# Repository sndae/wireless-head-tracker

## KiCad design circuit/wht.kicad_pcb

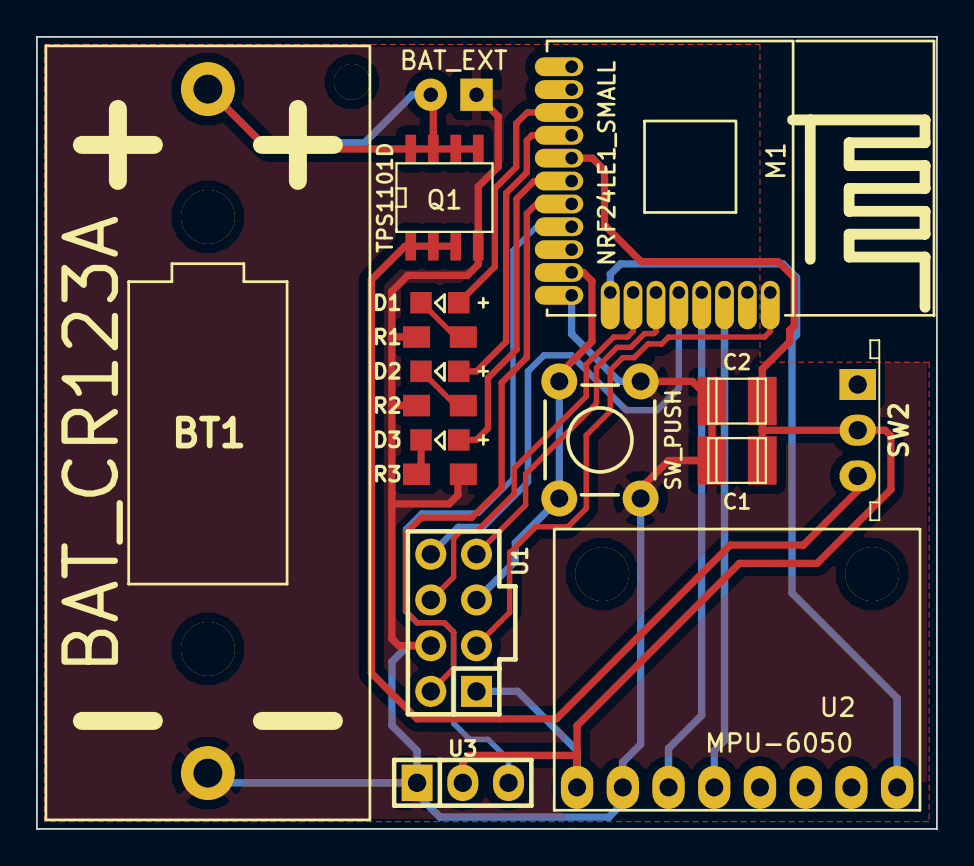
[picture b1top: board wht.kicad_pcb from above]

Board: 2 copper layers, 50.0 x 44.0 mm, 17 parts (0 on the bottom side), 20 nets.

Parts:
BT1: BAT_CR123A; CR123
BT2: BAT_EXT; BATTERY_EXT
C1: C; c_1210
C2: CP1; c_1210
D1, D2, D3: LED; LED-0805
M1: NRF24LE1_SMALL
Q1: TPS1101D; SOIC-8_N
R1, R2, R3: R; Resistor_SMD0805_HandSoldering
SW1: SW_PUSH; TACTILE-PTH
SW2: SWITCH_INV; ESP2010_switch
U1: NRF24LE1_PROG; Pin_Header_Straight_2x04
U2: MPU-6050; MPU6050
U3: UART; Pin_Header_Straight_1x03

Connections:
/FCSN: M1.15, U1.8
/FMISO: M1.14, U1.7
/FMOSI: M1.13, U1.6
/FSCK: M1.10, SW1.1, U1.5
/PROG: M1.7, U1.2
/RESET: M1.19, U1.3
/SCL: M1.16, U2.3
/SDA: M1.17, U2.4
GND: BT1.2, BT2.2, C1.2, C2.2, M1.11, Q1.4, R1.1, R2.1, R3.1, SW1.2, U1.4, U2.2, U3.1
unnamed: BT1.1, BT2.1, Q1.5, Q1.6, Q1.7, Q1.8
unnamed: D1.1, M1.3
unnamed: D1.2, R1.2
unnamed: D2.1, M1.4
unnamed: D2.2, R2.2
unnamed: D3.1, M1.6
unnamed: D3.2, R3.2
unnamed: M1.8, U3.3
unnamed: M1.12, U2.8
unnamed: Q1.1, Q1.2, Q1.3, SW2.3
VCC: C1.1, C2.1, M1.5, SW2.2, U1.1, U2.1, U3.2

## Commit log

2014-08-27 Initial directory structure.
2014-08-27 initial commit after project rename from edtracker-nrf
2014-08-27 added mcu-lib
2014-08-28 - added the stackup file for ZofPCB's 3D gerber viewer and the gerber packing batch file - removed the toner transfer markers for mounting holes from the PCB - tweaked the nRF module hole sizes from 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
2014-09-02 - small cleanup and comments
2014-09-05 - joined mpu_regs.h and mpu_defines.h - added comments
2014-09-08 - fixed a problem with the circuit project file; added library references - changed the project address on the bottom of the PCB
2014-10-22 added mpu_get_temperature - I need to get rid of floating points...
2014-10-23 added levels of auto-center added temperature sensor reading fixed a bug with combo box loading
2014-10-31 Added smaller CORDIC replacements for trig functions (atan2 and asin) This saves about 1800bytes of flash
2014-10-31 switched to integer CORDIC variants. they are much faster than the float version
2014-10-31 dropped the mymath module
2014-11-01 CORDIC tweaks and cleanup config dialog tweaks
2014-11-05 added MDU optimized 16 bit multiplication
2014-12-07 - mymath is back - cordic math is (temporarily) disabled due to possible accuracy problems - added drift comp tweak
2014-12-16 - fixed floating point precision to 3 digits in config - added experimental temperature dependent drift monitoring
2015-01-07 - dongle: changed driftSamples from int16_t to int32_t - dongle: commented out the temperature dependent drift calc - config: minimize to tray is now optional, controlled by MINIMIZE_TO_TRAY. current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
2015-01-08 - config: improved calibration feedback - config: yaw drift compensation display correction - tracker: added led cycle on power on/reset
2015-01-20 - added tracker transmit power selection - fixed Y axis problem
2015-01-21 - cleaned up the config dialog, with separate dongle and tracker groups - went back to Cordic versions of the asin and atan2 functions with slightly increased precision (by a factor of 1.8) - method 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
2015-01-21 - renamed settings.c/h to tracker_settings.c/h - renamed main.c to dongle.c
2015-01-22 fixed cordic overflow bug by reverting to the previous precision versions
2015-01-30 Created wiki page through web user interface.
2015-01-30 Edited wiki page WHT_flashing through web user interface.
2015-02-10 updated the WHT package download links
2015-02-18 the tracker is working on both 6050 and 9150
2015-02-18 space -> tab
2015-02-19 dropped reset_fifo()
2015-02-19 started rewriting proc_packet function
2015-02-19 integer drift compensation added linear and exponential axis response added
2015-02-21 added wrap_bias to fix centering around the sensor wrap point
2015-02-21 exponential response calculation changed from float to integer added numerical values to fields in the config
2015-02-22 adding cordic sin/cos, not there yet...
2015-02-23 cordic sin/cos seams to be working now removed the last float arithmetic from the dongle code
2015-05-09 Edited wiki page WHT_calib_config through web user interface.
2015-06-30 Migrating wiki contents from Google Code
